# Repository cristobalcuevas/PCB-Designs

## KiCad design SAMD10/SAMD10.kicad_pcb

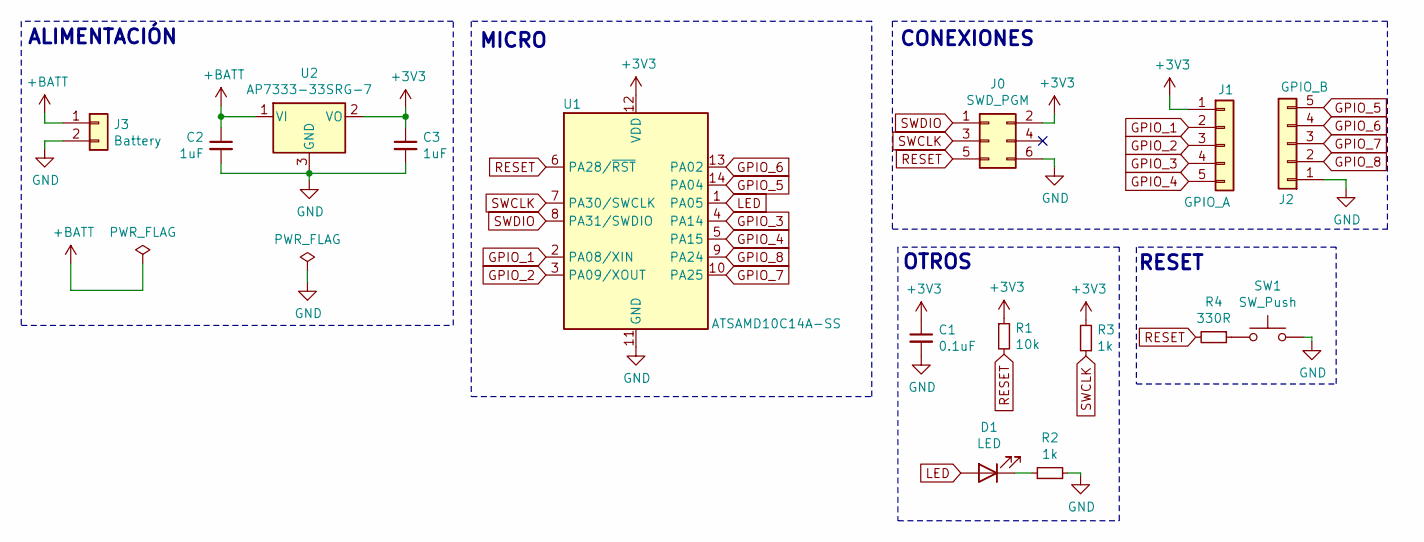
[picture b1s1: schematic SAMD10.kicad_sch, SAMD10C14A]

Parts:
C1: 0.1uF; C_0805_2012Metric
C2, C3: 1uF; C_0805_2012Metric
D1: LED; LED_0805_2012Metric_Pad1.15x1.40mm_HandSolder
J0: SWD_PGM; PinHeader_2x03_P2.54mm_Vertical
J1: GPIO_A; PinHeader_1x05_P2.54mm_Vertical
J2: GPIO_B; PinHeader_1x05_P2.54mm_Vertical
J3: Battery; JST_PH_B2B-PH-K_1x02_P2.00mm_Vertical
R1: 10k; R_0805_2012Metric
R2, R3: 1k; R_0805_2012Metric
R4: 330R; R_0805_2012Metric
SW1: SW_Push; SW_PUSH_6mm
U1: ATSAMD10C14A-SS; SOIC-14_3.9x8.7mm_P1.27mm
U2: AP7333-33SRG-7; SOT-23

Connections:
+3V3: C1.1, C3.1, J0.2, J1.1, R1.1, R3.2, U1.12 (VDD), U2.2 (VO)
+BATT: C2.1, J3.1, U2.1 (VI)
GND: C1.2, C2.2, C3.2, J0.6, J2.1, J3.2, R2.2, SW1.2, U1.11 (GND), U2.3 (GND)
GPIO_1: J1.2, U1.2 (PA08/XIN)
GPIO_2: J1.3, U1.3 (PA09/XOUT)
GPIO_3: J1.4, U1.4 (PA14)
GPIO_4: J1.5, U1.5 (PA15)
GPIO_5: J2.5, U1.14 (PA04)
GPIO_6: J2.4, U1.13 (PA02)
GPIO_7: J2.3, U1.10 (PA25)
GPIO_8: J2.2, U1.9 (PA24)
LED: D1.2 (A), U1.1 (PA05)
unnamed: D1.1 (K), R2.1
unnamed: R4.1, SW1.1
RESET: J0.5, R1.2, R4.2, U1.6 (PA28/~RST)
SWCLK: J0.3, R3.1, U1.7 (PA30/SWCLK)
SWDIO: J0.1, U1.8 (PA31/SWDIO)

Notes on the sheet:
MICRO
OTROS
RESET
ALIMENTACIÓN
CONEXIONES

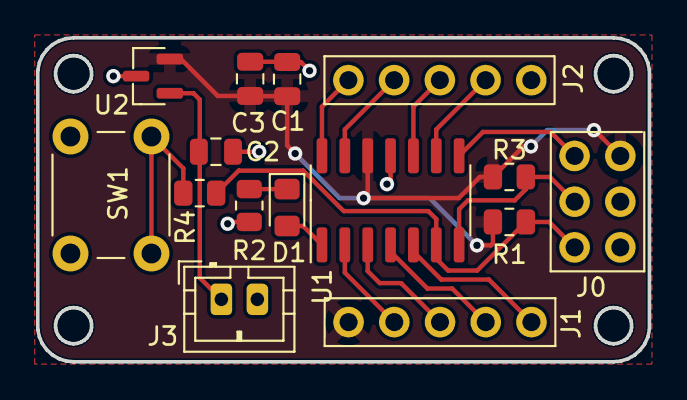
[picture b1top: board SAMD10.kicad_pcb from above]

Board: 2 copper layers, 34.0 x 18.0 mm, 15 parts (0 on the bottom side), 17 nets.

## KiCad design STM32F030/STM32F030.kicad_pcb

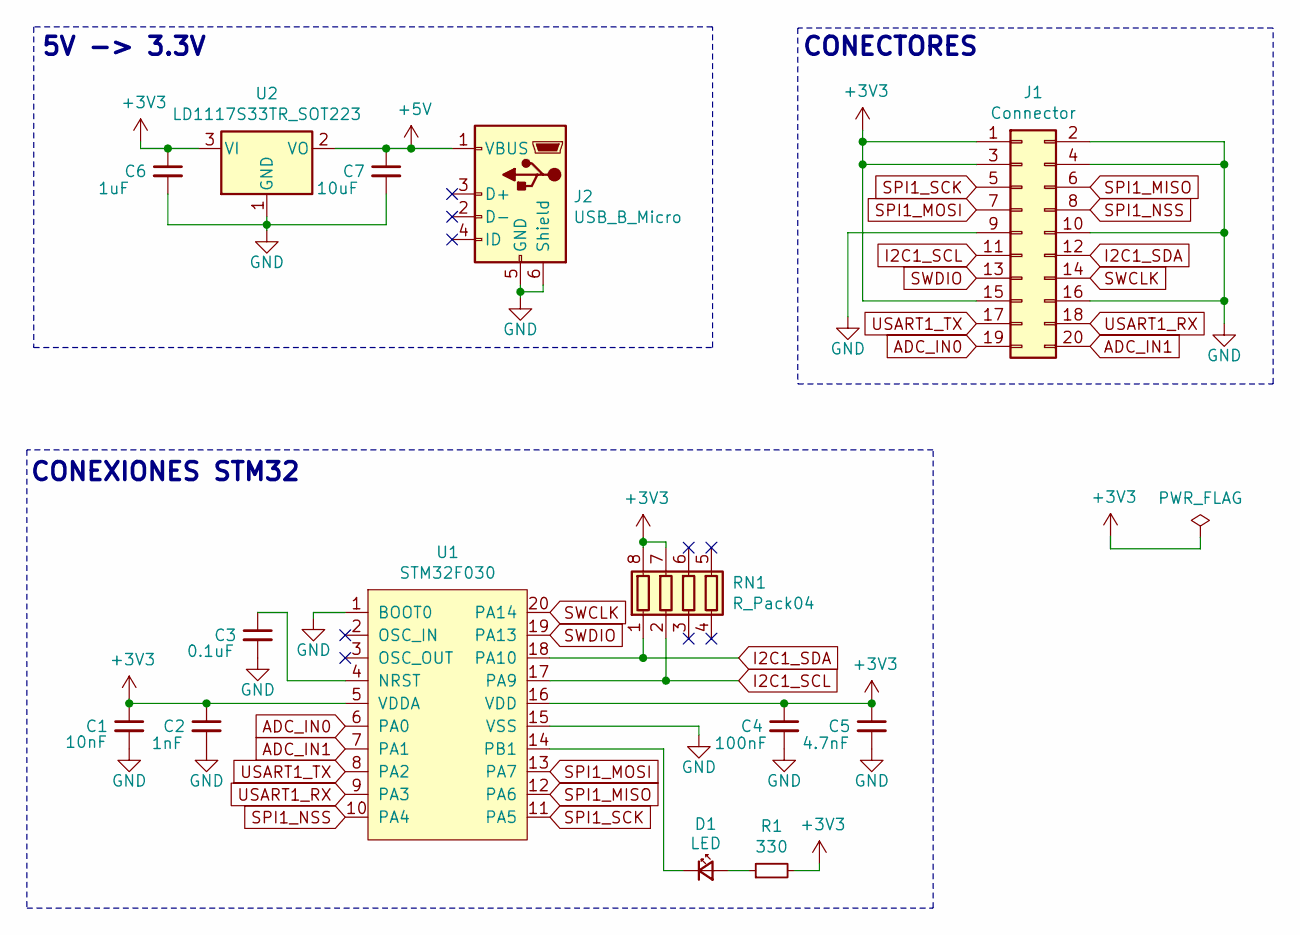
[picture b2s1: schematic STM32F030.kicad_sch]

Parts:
C1: 10nF; C_0805_2012Metric_Pad1.15x1.40mm_HandSolder
C2: 1nF; C_0805_2012Metric_Pad1.15x1.40mm_HandSolder
C3: 0.1uF; C_0805_2012Metric_Pad1.15x1.40mm_HandSolder
C4: 100nF; C_0805_2012Metric_Pad1.15x1.40mm_HandSolder
C5: 4.7nF; C_0805_2012Metric_Pad1.15x1.40mm_HandSolder
C6: 1uF; C_0805_2012Metric_Pad1.15x1.40mm_HandSolder
C7: 10uF; C_0805_2012Metric_Pad1.15x1.40mm_HandSolder
D1: LED; LED_0805_2012Metric_Pad1.15x1.40mm_HandSolder
J1: Connector; PinHeader_2x10_P2.54mm_Vertical
J2: USB_B_Micro; USB_Micro-B_Molex-105017-0001
R1: 330; R_0805_2012Metric_Pad1.15x1.40mm_HandSolder
RN1: R_Pack04; R_Array_Convex_4x0603
U1: STM32F030; TSSOP-20_4.4x6.5mm_P0.65mm
U2: LD1117S33TR_SOT223; SOT-223-3_TabPin2

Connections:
+3V3: C1.1, C2.1, C4.1, C5.1, C6.1, J1.1, J1.3, J1.15, R1.2, RN1.7 (R2.2), RN1.8 (R1.2), U1.5 (VDDA), U1.16 (VDD), U2.3 (VI)
+5V: C7.1, J2.1 (VBUS), U2.2 (VO)
ADC_IN0: J1.19, U1.6 (PA0)
ADC_IN1: J1.20, U1.7 (PA1)
GND: C1.2, C2.2, C3.2, C4.2, C5.2, C6.2, C7.2, J1.2, J1.4, J1.9, J1.10, J1.16, J2.5 (GND), J2.6 (Shield), U1.1 (BOOT0), U1.15 (VSS), U2.1 (GND)
I2C1_SCL: J1.11, RN1.2 (R2.1), U1.17 (PA9)
I2C1_SDA: J1.12, RN1.1 (R1.1), U1.18 (PA10)
unnamed: C3.1, U1.4 (NRST)
unnamed: D1.1 (K), U1.14 (PB1)
unnamed: D1.2 (A), R1.1
SPI1_MISO: J1.6, U1.12 (PA6)
SPI1_MOSI: J1.7, U1.13 (PA7)
SPI1_NSS: J1.8, U1.10 (PA4)
SPI1_SCK: J1.5, U1.11 (PA5)
SWCLK: J1.14, U1.20 (PA14)
SWDIO: J1.13, U1.19 (PA13)
USART1_RX: J1.18, U1.9 (PA3)
USART1_TX: J1.17, U1.8 (PA2)

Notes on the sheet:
CONEXIONES STM32
5V -> 3.3V
CONECTORES

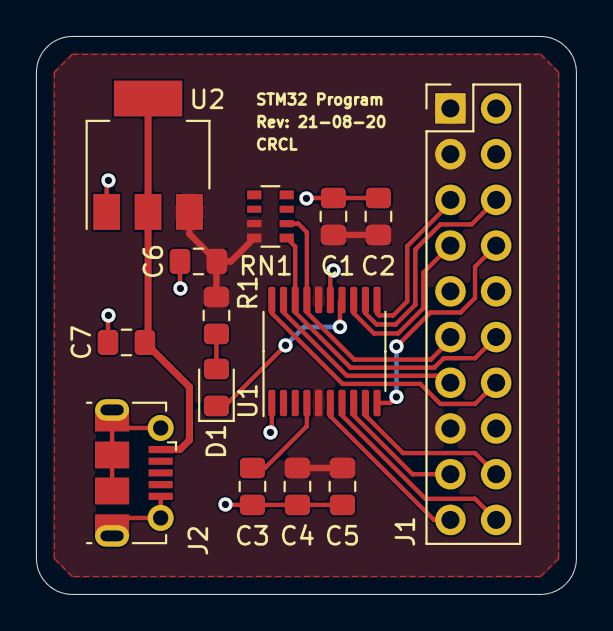
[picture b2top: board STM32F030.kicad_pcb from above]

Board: 2 copper layers, 30.0 x 31.0 mm, 14 parts (0 on the bottom side), 18 nets.

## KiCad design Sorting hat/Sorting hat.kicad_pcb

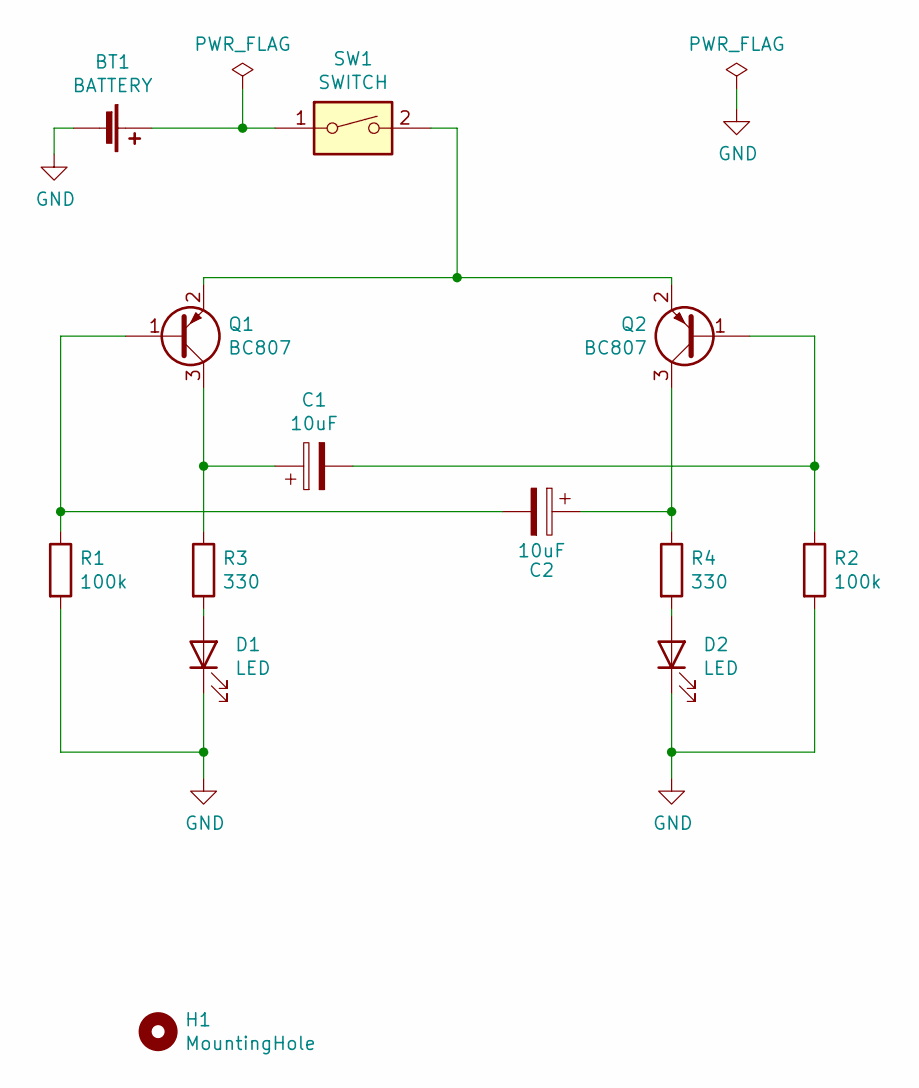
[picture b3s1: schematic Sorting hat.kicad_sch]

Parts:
BT1: BATTERY; MPD_BK-912-TR
C1, C2: 10uF; CP_Elec_4x5.4
D1, D2: LED; D_1206_3216Metric_Pad1.42x1.75mm_HandSolder
H1: MountingHole; MountingHole_2.2mm_M2
Q1, Q2: BC807; SOT-23
R1, R2: 100k; R_1206_3216Metric_Pad1.42x1.75mm_HandSolder
R3, R4: 330; R_1206_3216Metric_Pad1.42x1.75mm_HandSolder
SW1: SWITCH; A6S-1104-H

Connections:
GND: BT1.2 (-), D1.1 (K), D2.1 (K), R1.2, R2.2
unnamed: BT1.1 (+), SW1.1
unnamed: C1.1, Q1.3 (C), R3.1
unnamed: C1.2, Q2.1 (B), R2.1
unnamed: C2.1, Q2.3 (C), R4.1
unnamed: C2.2, Q1.1 (B), R1.1
unnamed: D1.2 (A), R3.2
unnamed: D2.2 (A), R4.2
unnamed: Q1.2 (E), Q2.2 (E), SW1.2

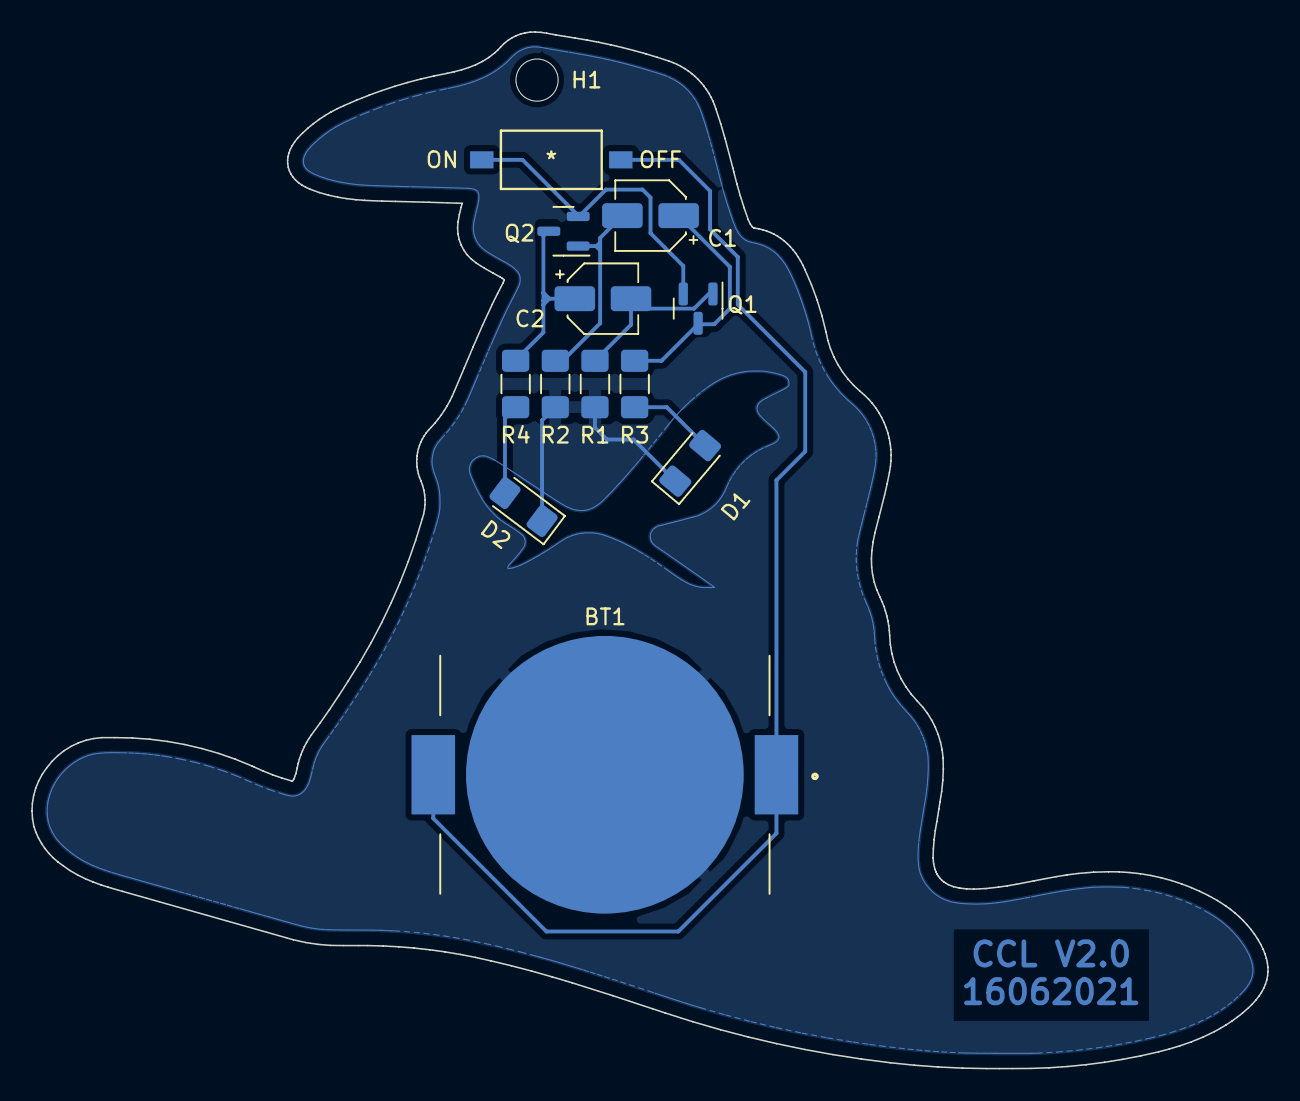
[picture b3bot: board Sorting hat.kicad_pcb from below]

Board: 2 copper layers, 79.1 x 66.4 mm, 13 parts (12 on the bottom side), 9 nets.

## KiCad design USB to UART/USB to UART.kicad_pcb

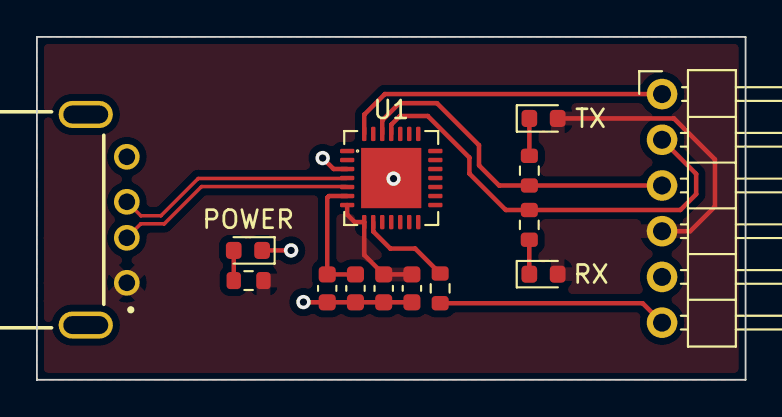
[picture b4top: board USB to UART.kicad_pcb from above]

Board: 2 copper layers, 39.4 x 19.0 mm, 14 parts (0 on the bottom side), 12 nets.

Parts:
C1, C4: 0.1u; C_0603_1608Metric
C2, C3: 4.7u; C_0603_1608Metric
D1: LED_RX; LED_0603_1608Metric
D2: LED_TX; LED_0603_1608Metric
D3: LED_POWER; LED_0603_1608Metric
J1: Connectors; PinHeader_1x06_P2.54mm_Horizontal
J2: USB_A; CONECTOR USB
R1: 1k; R_0603_1608Metric
R2, R3, R4: 220; R_0603_1608Metric
U1: CP2102N-A01-GQFN28; QFN-28-1EP_5x5mm_P0.5mm_EP3.35x3.35mm

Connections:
/CP2102N-GQFN28/3V3: C1.2, C2.1, J1.6, R1.1, U1.6 (VDD)
/CP2102N-GQFN28/D+: J2.3 (D+), U1.4 (D+)
/CP2102N-GQFN28/D-: J2.2 (D-), U1.5 (D-)
/CP2102N-GQFN28/DTR: J1.1, U1.28 (~DTR)
/CP2102N-GQFN28/RX: J1.2, R2.2, U1.25 (RXD)
/CP2102N-GQFN28/TX: J1.3, R3.2, U1.26 (TXD)
/USB/POWER: C3.2, C4.1, D1.2 (A), D2.2 (A), J1.4, J2.1 (VBUS), R4.1, U1.7 (REGIN), U1.8 (VBUS)
GND: C1.1, C2.2, C3.1, C4.2, D3.1 (K), J1.5, J2.4 (GND), J2.5 (Shield), U1.3 (GND), U1.29 (GND)
unnamed: D1.1 (K), R2.1
unnamed: D2.1 (K), R3.1
unnamed: D3.2 (A), R4.2
unnamed: R1.2, U1.9 (~RSTb)

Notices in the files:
parts and their libraries:
Copyright 2016 Accelerated Designs. All rights reserved.
